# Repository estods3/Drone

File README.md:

# Quadcopter with ROS/Wifi Flight Controller
This project is for a quadcopter using a WiFi controlled flight controller that you can control from your phone. The flight controller also interfaces with Robotic Operating System (ROS) to support live debugging and data logging with open-sourced industry tools.

&nbsp;&nbsp;&nbsp;&nbsp;&nbsp;&nbsp;

&nbsp;&nbsp;&nbsp;&nbsp;&nbsp;&nbsp;&nbsp;&nbsp;&nbsp;&nbsp;&nbsp;&nbsp;&nbsp;&nbsp;&nbsp;*Control from Phone/Web, Send Commands to Drone, View data live using ROS*

This repo provides the design files for the custom flight controller hardware and software as well as a parts list for building a working quadcopter with the custom flight controller.

## Flight Controller
The flight controller is a single-board design with accelerometers, microcontroller, wifi, battery monitoring, ESC connector, and status LEDs.

| Top | Bottom |
|---|---|
|  |  |

Gerber files used to order this PCB are included in the latest release, [here](https://github.com/estods3/Drone/releases/tag/V1.0)

Parts list to assembly final board can be found in the BOM, [here](https://github.com/estods3/Drone/blob/main/HW/BOM.md)

### Hardware Features:
1. 2-Layer design with top and bottom ground plane.
2. Antenna clearance complies with ESP32 specification to help prevent interference to WiFi Signal.
3. IMU orientation aligned with drone frame. Design supports both ISO-20600 and MPU2060 IMU components.

4. Standard 30.5mm by 30.5mm flight controller mounting pattern
5. Eectrical interface using JST-SH 8 Pin connector (compatible with SpeedyBee BL32 50A V3 ESC for stacked ESC/Flight Controller layout).
6. Single Supply (3S LiPo) powering both ESC as well as flight controller (Powered through JST-SH Connector).
7. Status LEDs to quickly see if Wifi is connected, if software is recieving commands from remote controller, etc.
8. Built-in ESC Firmware debug interface with BLHeli Suite (Coming Soon).

### Software Features:
1. Arduino-based C++.
2. Wifi controlled using a phone with browser, provides battery life status as well as controls for Up, Down, Left, Right, etc.
3. Robotic Operating System (ROS) interface provides live feed of IMU data, flight controller status, user commands, and ESC throttle to each motor. (must have variable USE_ROS = True).
4. PID-based flight stability controller (Coming Soon).
5. "Testing Mode" allows user to test throttle of each motor, calibrate PID controller without reflashing flight controller (Coming Soon).

#### IMU Calibration:
Run script to compute IMU calibration:

```
Reading sensors for first time...
Results of measurements a/g:	0.23	0.53	12.09	-0.03	-0.02	0.01

Calculating offsets...
Results of measurements a/g:	-0.00	-0.00	9.81	0.00	0.00	0.00
...

Calibration successful!
Results of measurements a/g:	-0.01	0.00	9.81	0.00	0.00	-0.00

FINISHED!

Sensor readings with offsets:	-0.01	0.00	9.81	0.00	0.00	-0.00
Your offsets:	-0.23	-0.53	-2.29	0.03	0.02	-0.01
```

#### ROS Interface:
Create a ROS interface where you can view and log data from your quadcopter live.

From a PC with ROS installed, run:

```
roscore
```

In another terminal from PC run:

```
roslaunch rosserial_server socket.launch

```

This will create a rosserial server to interface with the nodeMCU controller.

In another terminal launch:
```
rqt
```

to see the following visualization of your drone's data!

#### User Interface/Remote Control
The UI for remote control is deployed over WiFi to a static IP address accessible to a phone logged on to the Flight Controller's hosted WiFi network.

Commands available:

Up, Down, Left, Right, Forward, Backward, Rotate Left, Rotate Right

If not command is given, the drone will hold in place.

## Prototype
This flight controller was tested with a 5 inch FPV Frame, although other frames could be used with tuning of the flight controller.

#### Test Quadcopter Specs:

Physical Size: ~450 grams, 5 inch FPV

Frame: 

Battery Size: 3S Lipo

Motors: brushless DC

ESC: [Speedybee 4-in-1 ESC](https://www.speedybee.com/speedybee-f7-v3-bl32-50a-4-in-1-esc/)

For full BOM, click [here](https://github.com/estods3/Drone/blob/main/HW/BOM.md)

#### ESC Firmware with BLHeli:
Using Arduino Nano as an interface (4wArduino_Nano__16_MULTIv20005.hex) with ESC plugged into pin D4. The opposite corner motors were set to clockwise and counter-clockwise, respectively. NOTE: this can be done in BLHeli software to correct the direction of the motor if the motor was wired incorrectly to the ESC. Brushless DC motors have 3 wires A, B, and C and the order determines the direction.

## Resources:
PID Controller: 
https://github.com/0xekez/arduino-drone-pid/blob/master/pid_v2_in_arduino/pid_v2_in_arduino.ino
https://www.youtube.com/watch?v=hGcGPUqB67Q
https://www.youtube.com/watch?v=wkfEZmsQqiA
https://github.com/bolandrm/rmb_multicopter

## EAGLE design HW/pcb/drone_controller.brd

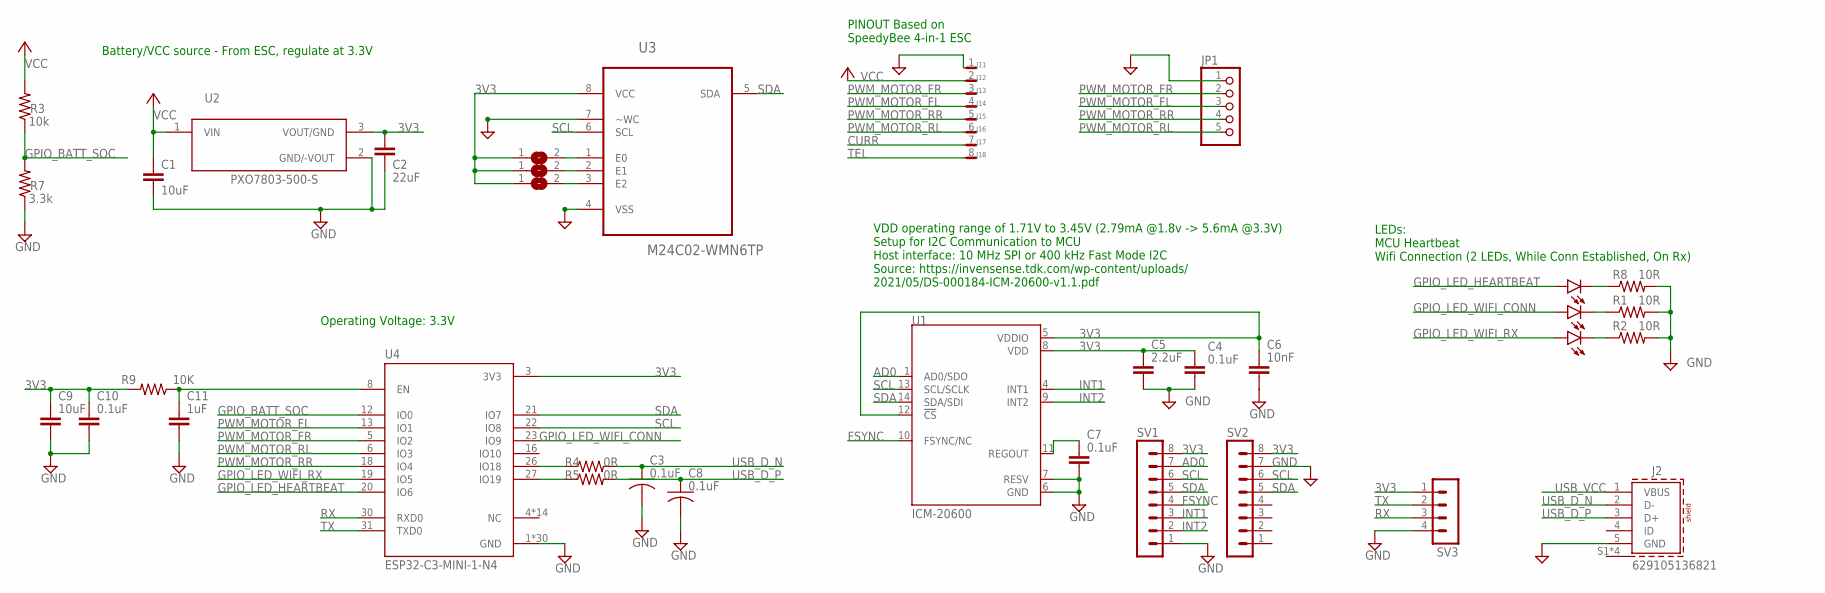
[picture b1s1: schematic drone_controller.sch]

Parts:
C1, C9: 10uF; C2.5-3
C2: 22uF; C2.5-3
C3, C8: 0.1uF; C0603
C4, C7, C10: 0.1uF; C2.5-3
C5: 2.2uF; C2.5-3
C6: 10nF; C2.5-3
C11: 1uF; C2.5-3
J1: SM08B-SRSS-TB
J2: 629105136821
JP1: PINHD-1X5; 1X05
LED4, LED5, LED6: LED5MM
R1, R2, R8: 10R; 0204/7
R3: 10k; 0204/7
R4, R5: 0R; 0204/7
R7: 3.3k; 0204/7
R9: 10K; 0204/7
SJ1, SJ2, SJ3: SJ
SV1, SV2: MA08-1
SV3: MA04-1
U1: ICM-20600; PQFN50P250X300X97-14N
U2: PXO7803-500-S; CONV_PXO7803-500-S
U3: M24C02-WMN6TP; SOIC127P600X175-8N
U4: ESP32-C3-MINI-1-N4; XCVR_ESP32-C3-MINI-1-N4

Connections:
3V3: C2.1, C4.1, C5.1, C6.1, C9.1, C10.1, R9.2, SJ1.1, SJ2.1, SJ3.1, SV1.8, SV2.8, SV3.1, U1.5 (VDDIO), U1.8 (VDD), U1.12 (!CS), U2.3 (VOUT/GND), U3.8 (VCC), U4.3 (3V3)
AD0: SV1.7, U1.1 (AD0/SDO)
CURR: J1.7
FSYNC: SV1.4, U1.10 (FSYNC/NC)
GND: C1.2, C2.2, C3.2, C4.2, C5.2, C6.2, C7.2, C8.2, C9.2, C10.2, C11.2, J1.1, J2.5 (GND), JP1.1, R1.2, R2.2, R7.1, R8.2, SV1.1, SV2.7, SV3.4, U1.6 (GND), U1.7 (RESV), U2.2 (GND/-VOUT), U3.4 (VSS), U3.7 (~WC), U4.1 (GND), U4.2 (GND), U4.11 (GND), U4.14 (GND), U4.36 (GND), U4.37 (GND), U4.38 (GND), U4.39 (GND), U4.40 (GND), U4.41 (GND), U4.42 (GND), U4.43 (GND), U4.44 (GND), U4.45 (GND), U4.46 (GND), U4.47 (GND), U4.48 (GND), U4.49_1 (GND), U4.49_2 (GND), U4.49_3 (GND), U4.49_4 (GND), U4.49_5 (GND), U4.49_6 (GND), U4.49_7 (GND), U4.49_8 (GND), U4.49_9 (GND), U4.50 (GND), U4.51 (GND), U4.52 (GND), U4.53 (GND)
GPIO_BATT_SOC: R3.1, R7.2, U4.12 (IO0)
GPIO_LED_HEARTBEAT: LED4.A, U4.20 (IO6)
GPIO_LED_WIFI_CONN: LED5.A, U4.23 (IO9)
GPIO_LED_WIFI_RX: LED6.A, U4.19 (IO5)
INT1: SV1.3, U1.4 (INT1)
INT2: SV1.2, U1.9 (INT2)
unnamed: C7.1, U1.11 (REGOUT)
unnamed: C11.1, R9.1, U4.8 (EN)
unnamed: SJ1.2, U3.1 (E0)
unnamed: SJ2.2, U3.2 (E1)
unnamed: SJ3.2, U3.3 (E2)
unnamed: LED5.K (C), R1.1
unnamed: LED4.K (C), R8.1
unnamed: LED6.K (C), R2.1
PWM_MOTOR_FL: J1.4, JP1.3, U4.13 (IO1)
PWM_MOTOR_FR: J1.3, JP1.2, U4.5 (IO2)
PWM_MOTOR_RL: J1.6, U4.6 (IO3)
PWM_MOTOR_RR: J1.5, JP1.4, U4.18 (IO4)
RX: SV3.3, U4.30 (RXD0)
SCL: SV1.6, SV2.6, U1.13 (SCL/SCLK), U3.6 (SCL), U4.22 (IO8)
SDA: SV1.5, SV2.5, U1.14 (SDA/SDI), U3.5 (SDA), U4.21 (IO7)
TEL: J1.8
TX: SV3.2, U4.31 (TXD0)
USB_D_N: C3.1, J2.2 (D-), R4.2
USB_D_P: C8.1, J2.3 (D+), R5.2
USB_RD_N: R4.1, U4.26 (IO18)
USB_RD_P: R5.1, U4.27 (IO19)
USB_VCC: J2.1 (VBUS)
VCC: C1.1, J1.2, R3.2, U2.1 (VIN)

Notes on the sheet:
Battery/VCC source - From ESC, regulate at 3.3V
VDD operating range of 1.71V to 3.45V (2.79mA @1.8v -> 5.6mA @3.3V) Setup for I2C Communication to MCU Host interface: 10 MHz SPI or 400 kHz Fast Mode I2C Source: https://invensense.tdk.com/wp-content/uploads/ 2021/05/DS-000184-ICM-20600-v1.1.pdf
LEDs: MCU Heartbeat Wifi Connection (2 LEDs, While Conn Established, On Rx)
Operating Voltage: 3.3V
PINOUT Based on SpeedyBee 4-in-1 ESC

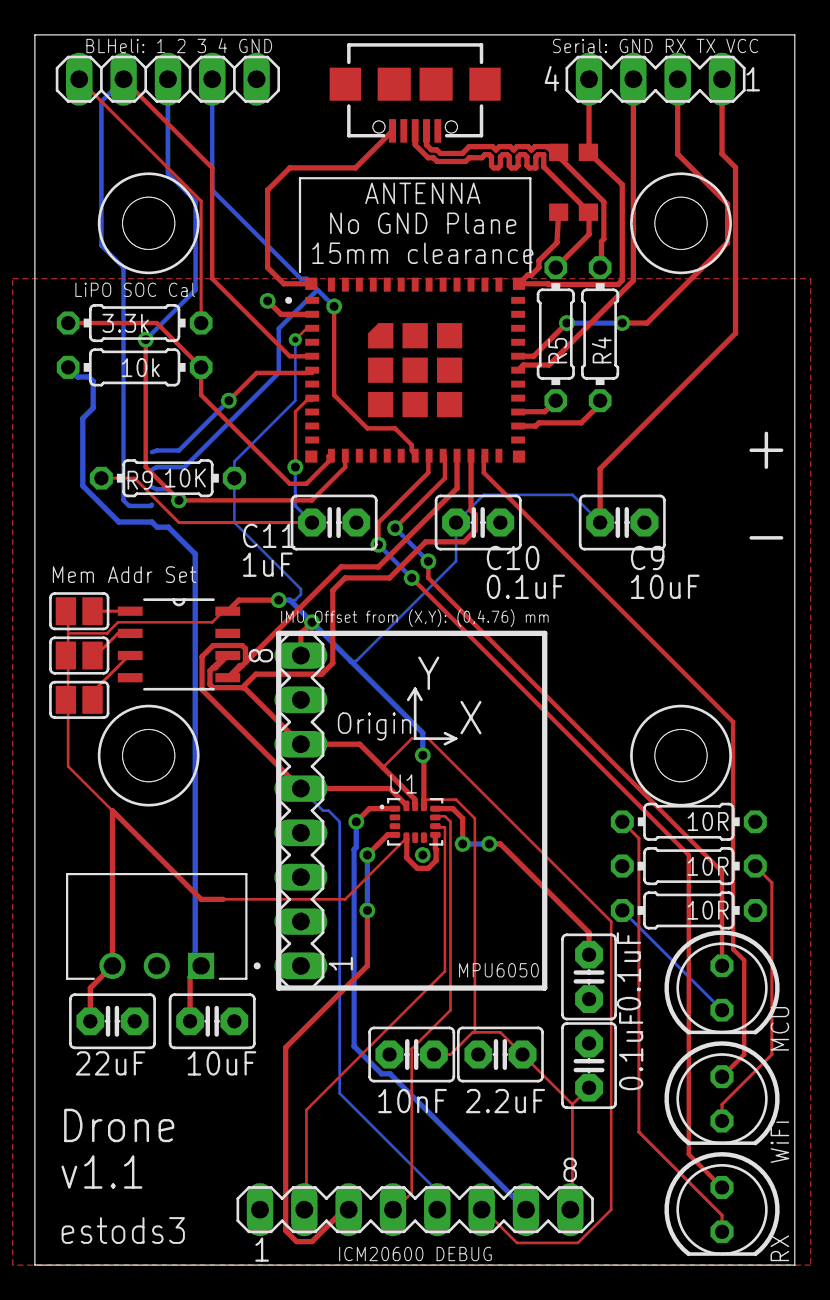
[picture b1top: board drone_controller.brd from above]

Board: 2 copper layers, 43.5 x 70.5 mm, 35 parts (1 on the bottom side), 31 nets.

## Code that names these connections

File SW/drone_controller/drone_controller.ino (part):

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//Potential Solution: Add RST button circuitry to PCB which triggers reset of NodeMCU + temporarily turns off motor drivers.
int i2c_scl = D1; //USED FOR I2C, comes from hardware variant definition for NodeMCU
int i2c_sda = D2; //USED FOR I2C, comes from hardware variant definition for NodeMCU
int gpio_led_heartbeat = D3;
int gpio_led_wifi_rx = D4;
int gpio_led_wifi_conn = D7; // GPIO13
//NOTE: D4 is the same as the BUILT IN LED pin. The built in LED will pulse opposite D4 HIGH/LOW Status.

// WiFI CALIBRATION
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};

// Instantiate Global Variables from Above.
heartbeatLED heartbeat(gpio_led_heartbeat, 100, 400);

// FUNCTION: Connect to Wifi
// Description: initialize connection to specified wifi network
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  } else {
    wifi_status_connected = WiFi.status() == WL_CONNECTED;
  }
  digitalWrite(gpio_led_wifi_conn, wifi_status_connected);
  return wifi_status_connected;
}

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      inputMessage = request->getParam(PARAM_INPUT)->value();
      stopvalue = 1;
      Serial.println("/stop = " + String(stopvalue));
      digitalWrite(gpio_led_wifi_rx, HIGH);
      delay(wifi_rx_flash_duration_ms);
      digitalWrite(gpio_led_wifi_rx, LOW);
    }
    else {
      inputMessage = "No message sent";
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      inputMessage = request->getParam(PARAM_INPUT)->value();
      armvalue = 1;
      Serial.println("/arm = " + String(armvalue));
      digitalWrite(gpio_led_wifi_rx, HIGH);
      delay(wifi_rx_flash_duration_ms);
      digitalWrite(gpio_led_wifi_rx, LOW);
    }
    else {
      inputMessage = "No message sent";
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    Serial.println("/PID = " + String(Ki[YAW]) + "," + String(Ki[PITCH]) + "," + String(Ki[ROLL]));
    Serial.println("/PID = " + String(Kd[YAW]) + "," + String(Kd[PITCH]) + "," + String(Kd[ROLL]));
    request->send(200, "text/plain", "OK");
    digitalWrite(gpio_led_wifi_rx, HIGH);
    delay(wifi_rx_flash_duration_ms);
    digitalWrite(gpio_led_wifi_rx, LOW);
  });
    
  server.begin();
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  Serial.println();

  // Initializing LED Pins + Heartbeat LED
  pinMode(gpio_led_wifi_conn, OUTPUT);
  pinMode(gpio_led_wifi_rx, OUTPUT);
  pinMode(gpio_battery_level, INPUT);
  digitalWrite(gpio_led_wifi_conn, LOW);
  digitalWrite(gpio_led_wifi_rx, LOW);
  heartbeat.Update();

  // Initialize ESCs
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
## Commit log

2023-03-16 added BOM
2023-03-16 added test files for tests performed with NodeMCU. Tested LED blinking with GPIO and controlling over WIFI, Accelerometer over I2C and built in LED. Have not yet tested ROS Test talker.py
2023-03-17 added SW config.txt to gitignore
2023-03-17 ros nodemcu example no longer needed
2023-03-17 tested running ROS on host PC with a roscore and rosserial server. Connected to nodeMCU over wifi and could see results of example Hello World message
2023-03-17 initial version of drone controller with GUI commands working, ROS server implemented.
2023-03-18 updated readme. added LEDs to drone SW
2023-03-19 implemented heartbeat LED in SW. Adjusted position of MCU on board to account for loss from GND plane. Removed unneeded battery indicators (only one LED for Low BATT).
2023-03-20 tested PWM from NodeMCU. working on all pins
2023-03-20 split up functionality into functions. added pinout for LEDs, PWM.
2023-03-20 implemented pinout into schematic. added LED interface
2023-03-22 implemented ros IMU messages. still testing.
2023-03-22 tested ROS rosserial test with NodeMCU. was able to verify seeing data using rostopic echo on host PC running roscore
2023-03-23 WORKING VERSION: drone controller with ROS reporting heartbeat and IMU data over ROS network. display is working in RQT and populating in RVIZ. more work needed to display in correct coordinate syste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
2023-03-24 Working Version. Drone Controller with IMU, heartbeat, wifi connection status, and command from GUI Server all running simultaniously on target MCU with comms wirelessly with ROS. Host PC running ROS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
2023-06-13 added motor control to drone controller for testing. adding ESC interface using Servo library. added GUI options to Init ESC and +/- throttle for a single ESC. WORKING VERSION on breadboard hardware 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
2023-06-13 working on PCB design. added 3.3v to 5v level shifter, but it is not needed. tested NodeMCU to SpeedyBee ESC and was able to communicate using Servo Library without needed PWM voltage to increase fro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
2023-06-13 added useful test files to testing ESCs and calibrating MPU6050.
2023-06-14 removed 3.3V to 5V level shifter. not needed for this ESC (SpeedyBee 4-in-1 ESC). Placed components on board in more organized layout. Routed Board. All Airwires routed. Added Ground planes with stic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
2023-06-14 implemented battery life into drone controller and GUI. tested and calibrated. working correctly.
2023-06-14 ordered PCB
2023-06-20 Tested IMU with both Arduino Serial logging and ROS. both worked correctly and were being plotted. Did side by side comparison of Serial data and ROS data plotting and both responded to movement of t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
2023-06-20 briefly was able to control ESC with similar code in this commit. seems to be hardware issue with connection to ESC. Also, intermittent connection to MPU IMU. Need to do full hardware test where ESC 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
2023-07-12 implemented new HTML front end for drone controller with CSS and slider bars to adjust throttle for elevation, yaw, and forward/backward. none of these are implemented with PID flight controller yet.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
2023-07-13 added elevation,yaw,and forward/backward controls to ROS and front end. not yet tied into PID controller. Implemented stop and arm buttons on front end and improbed look/feel of front end
2023-07-13 added images
2023-07-15 modified IMU calibration script. implemented Adafruit library. tested and imported calibration offsets into main drone_controller code
2023-08-29 ordered V1.1 of drone PCB
2023-08-29 updated images
2023-12-11 added settings section of UI to allow for updating PID values.
2023-12-11 code cleanup. added new support for measurements from IMU into PID. not yet finished
2023-12-11 working on drone. can mode properly. need to test if it works with motors connected to power
2023-12-18 added 2 wifi modes to allow AccessPoint or connect to existing network (useful for wifi debugging with ROS). Tested with home WIFI and ROS with RQT. all 4 ESCs working and orientation visualization o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
2023-12-19 implemented complementary filter for IMU. working in all 3 dimensions. tested with quarternion function to communicate message onto ROS network
2024-02-03 added front end functionality to pull from currently saved PID cal values. adjusted top throttle setting for lift. adjusted yaw measurement to be negative to match intented coordinate system (in comm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
2025-06-09 added docs folder
2025-06-09 added ROS files
2025-06-09 misc HW file
2025-06-09 added video

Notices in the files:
parts and their libraries:
Eagle_WR-USB: Copyright: Würth Elektronik
